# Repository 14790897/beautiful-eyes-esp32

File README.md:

# Beautiful Eyes - 嵌入式眼睛动画项目

一个运行在 ESP32-C3 上的眼睛动画项目，支持多种风格的眼睛效果。双屏同步显示，营造立体生动的眼睛效果。

## ✨ 特性

### 七种眼睛风格

#### 1. 普通眼睛 (Normal Eye)
- 白色眼白，棕色虹膜
- 自然的眨眼动画
- 简单的睫毛和血管纹理
- 标准的眼球移动

#### 2. 恶魔眼睛 (Demon Eye)
- 深灰色巩膜，红色虹膜
- **竖瞳设计** - 猫科动物般的竖直瞳孔
- **发光效果** - 脉动的发光光晕
- **心形高光** - 独特的反光效果
- 更快速、更主动的眼神移动

#### 3. 美丽女生眼睛 (Beautiful Eye)
- 纯净的眼白
- **多层虹膜渐变** - 温柔的棕色渐变
- **淡粉色眼影** - 精致的眼妆效果
- **深棕色眼线** - 从眼头到眼尾的渐变眼线
- **浓密睫毛** - 18根上睫毛 + 12根下睫毛
- **三重高光** - 主高光、淡蓝色次高光、下方小高光
- **闪亮动画** - 虹膜上的动态闪光点
- 温柔优雅的眨眼动画

#### 4. 赛博朋克眼睛 (Cyber Eye) 🆕
- 深蓝灰色巩膜，青色虹膜
- **HUD显示** - 科幻感十足的抬头显示界面
- **扫描线** - 动态扫描线效果
- **网格纹理** - 机械感的虹膜网格
- **数据流动画** - 随机数据流显示
- **准星瞄准** - 红色瞄准准星
- 快速精确的机械眼球移动

#### 5. 星空宇宙眼睛 (Cosmic Eye) 🆕
- 深紫灰巩膜，神秘宇宙色
- **星云渐变** - 多层星云色彩渐变
- **星系旋转** - 虹膜内的星系螺旋效果
- **闪烁星星** - 随机分布的闪烁星点
- **流星划过** - 偶尔出现的流星效果
- **脉冲发光** - 神秘的发光脉动
- 缓慢优雅的眼球移动

#### 6. 显轮眼 (Sharingan - Wheel Eye) 🆕
- 纯白巩膜，鲜红色虹膜
- **三勾玉设计** - 经典的三勾玉图案
- **勾玉旋转** - 持续旋转的勾玉动画
- **红色发光** - 强烈的红色光晕效果
- **黑色轮廓** - 清晰的图案轮廓线
- 凌厉快速的眼神移动

#### 7. 星瞳眼 (Anime Star Pupil Eye) 🆕
- 纯白巩膜，粉紫色虹膜
- **五角星瞳孔** - 可爱的星形瞳孔设计
- **多层渐变** - 粉色系多层虹膜渐变
- **闪烁效果** - 虹膜周围的闪烁星光
- **粉色发光** - 梦幻的粉色光晕
- **星星旋转** - 瞳孔星星的缓慢旋转
- 活泼灵动的眼球移动

### 真实动画效果
- 自然的眨眼动画
- 灵动的眼球移动
- 精致的虹膜渐变
- 多重高光效果
- 双屏同步显示
- **共享 Sprite** - 单个图像缓冲区双屏复用，节省内存

### 简单交互
- **单击** BOOT 按钮 (GPIO9) - 向下翻页(下一个眼睛类型)
- **双击** BOOT 按钮 (GPIO9) - 向上翻页(上一个眼睛类型)
- 即按即切，无需重启
- 可配置的按钮响应参数

## 🔧 硬件要求

- **开发板**: ESP32-C3 (推荐: AirM2M Core ESP32-C3)
- **显示屏**: 2块 ST7789 240x240 LCD (双屏同步显示)
- **数据线**: USB Type-C

### 引脚连接

#### 共享 SPI 引脚
| SPI 引脚 | ESP32-C3 GPIO |
|---------|---------------|
| SCLK    | 2             |
| MOSI    | 3             |

#### 屏幕一引脚
| LCD 引脚 | ESP32-C3 GPIO |
|---------|---------------|
| DC      | 10            |
| CS      | 6             |
| RST     | 7             |

#### 屏幕二引脚
| LCD 引脚 | ESP32-C3 GPIO |
|---------|---------------|
| DC      | 1             |
| CS      | 0             |
| RST     | 4             |

#### 按钮
| 功能     | ESP32-C3 GPIO |
|---------|---------------|
| BOOT 按钮 | 9           |

## 🚀 快速开始

### 方法 1: 下载预编译固件 (推荐)

1. 前往 [Releases](https://github.com/14790897/beautiful-eyes-esp32/releases) 页面
2. 下载最新版本的固件包
3. 解压并按照 `FLASH_GUIDE.md` 说明烧录

**使用 esptool 烧录:**
```bash
pip install esptool

esptool.py --chip esp32c3 --port COM5 --baud 460800 \
  --before default_reset --after hard_reset write_flash \
  0x0 bootloader.bin \
  0x8000 partitions.bin \
  0x10000 firmware.bin
```

### 方法 2: 从源码构建

#### 前置要求
- Python 3.7+
- PlatformIO Core

#### 构建步骤

```bash
# 克隆仓库
git clone https://github.com/14790897/beautiful-eyes-esp32.git
cd beautiful-eyes-esp32

# 安装 PlatformIO
pip install platformio

# 编译
pio run

# 编译并上传
pio run -t upload

# 查看串口输出
pio device monitor
```

## 📖 使用说明

### 切换眼睛类型

#### 单击 BOOT 按钮 (GPIO9) - 向下翻页

```
普通眼睛 → 魅魔眼睛 → 美丽女生眼睛 → 赛博朋克眼睛 → 星空宇宙眼睛 → 显轮眼 → 星瞳眼 → (循环)
```

#### 双击 BOOT 按钮 (GPIO9) - 向上翻页

```
普通眼睛 → 星瞳眼 → 显轮眼 → 星空宇宙眼睛 → 赛博朋克眼睛 → 美丽女生眼睛 → 魅魔眼睛 → (循环)
```

串口会输出当前切换的眼睛类型。

### 双击设置说明

如果双击不灵敏，可以在 `src/main.cpp` 中调整以下参数：

```cpp
bootButton.setClickMs(300);   // 单击判定时间(ms) - 越小越快识别
bootButton.setIdleMs(600);    // 双击间隔时间(ms) - 越大越容易触发
```

## 📁 项目结构

```
beautiful-eyes/
├── .github/
│   └── workflows/          # GitHub Actions CI/CD
│       ├── build.yml       # 自动构建工作流
│       └── release.yml     # 版本发布工作流
├── include/
│   ├── eyes/               # 眼睛模块头文件
│   │   ├── normal/         # 普通眼睛
│   │   ├── demon/          # 魅魔眼睛
│   │   ├── beautiful/      # 美丽女生眼睛
│   │   ├── cyber/          # 赛博朋克眼睛
│   │   ├── cosmic/         # 星空宇宙眼睛
│   │   ├── wheel/          # 显轮眼
│   │   └── star/           # 星瞳眼
│   ├── Config.h            # 全局配置
│   └── Display.h           # 显示驱动
├── src/
│   ├── eyes/               # 眼睛模块实现
│   ├── Display.cpp
│   └── main.cpp
├── docs/
│   ├── FILE_STRUCTURE.md   # 文件结构说明
│   └── CI_CD_GUIDE.md      # CI/CD 指南
└── platformio.ini          # PlatformIO 配置
```

详细说明: [FILE_STRUCTURE.md](docs/FILE_STRUCTURE.md)

## 🔄 CI/CD

本项目使用 GitHub Actions 实现自动化构建和发布:

### 自动构建
- ✅ 推送到 `main` 或 `dev` 分支时自动构建
- ✅ Pull Request 时自动构建验证
- ✅ 构建产物保留 30 天，可在 Actions 页面下载

### 自动发布
- ✅ 创建 Git Tag 自动触发发布流程
- ✅ 自动生成完整的烧录指南
- ✅ 自动打包固件、bootloader、分区表
- ✅ 生成 SHA256 校验和

### 如何发布新版本

```bash
# 创建版本标签
git tag -a v1.0.0 -m "Release version 1.0.0"

# 推送标签触发发布
git push origin v1.0.0
```

详细说明请查看 [CI/CD 指南](docs/CI_CD_GUIDE.md)

## 🛠️ 开发指南

### 添加新的眼睛类型

1. 在 `include/eyes/` 和 `src/eyes/` 创建新目录
2. 创建眼睛数据类 (如 `NewEye.h/cpp`)
3. 创建渲染器 (如 `NewEyeRenderer.h/cpp`)
4. 在 `Config.h` 添加配置参数
5. 在 `main.cpp` 集成新类型

详细步骤: [FILE_STRUCTURE.md](docs/FILE_STRUCTURE.md)

### 自定义配置

编辑 `include/Config.h` 可修改:
- **硬件引脚配置** - 双屏幕的 SPI、DC、CS、RST 引脚
- **颜色配置** - 每种眼睛类型独立的颜色方案
- **动画参数** - 眨眼频率、移动速度、旋转速度等
- **特效参数** - 发光强度、闪烁速度、扫描线速度等
- **睫毛参数** - 数量和长度

编辑 `src/main.cpp` 可修改:
- **按钮响应参数**:
  - `setClickMs()` - 单击判定时间
  - `setIdleMs()` - 双击间隔时间
  - `setDebounceMs()` - 去抖动时间
  - `setPressMs()` - 长按判定时间

### 代码规范

- 使用完整的 include 路径: `#include "eyes/normal/Eye.h"`
- 每种眼睛类型独立目录
- 配置参数统一放在 `Config.h`

## 🐛 故障排除

### 编译错误
```bash
# 清理构建缓存
pio run -t clean
# 重新构建
pio run
```

### 烧录失败
- 确保设备已连接且驱动已安装
- 尝试按住 BOOT 按钮再烧录
- 降低波特率: `pio run -t upload --upload-speed 115200`

### 屏幕无显示
- 检查引脚连接是否正确
- 验证显示屏电源供应
- 查看串口输出: `pio device monitor`

### 眼睛闭合不动
- 这是旧版本的 bug，已在最新版修复
- 更新到最新固件即可

### 双击不工作或难以触发
- 检查串口输出是否有双击日志
- 调整 `setIdleMs()` 参数 (增大到 800 或 1000ms)
- 调整 `setClickMs()` 参数 (减小到 200 或 250ms)
- 确保两次点击间隔在设定时间内
- 示例代码在 `src/main.cpp` 的 `setup()` 函数中

## 📊 性能指标

- **显示屏数量**: 2块 (双屏同步)
- **眼睛类型**: 7种不同风格
- **共享内存**: 单个 sprite 双屏共用，节省内存
- **帧率**: ~20 FPS
- **眨眼间隔**: 2-8秒 (不同眼睛类型可配置)
- **按钮响应**:
  - 单击判定: 300ms
  - 双击间隔: 600ms
  - 去抖动: 50ms

## 🤝 贡献

欢迎贡献! 步骤:

1. Fork 本仓库
2. 创建特性分支 (`git checkout -b feature/AmazingFeature`)
3. 提交更改 (`git commit -m 'Add some AmazingFeature'`)
4. 推送到分支 (`git push origin feature/AmazingFeature`)
5. 开启 Pull Request

## 📝 更新日志

查看 [Releases](https://github.com/14790897/beautiful-eyes-esp32/releases) 获取完整更新日志。

### 最新更新
- ✅ 添加双击向上翻页功能
- ✅ 添加星瞳眼效果 - 五角星瞳孔，粉色梦幻
- ✅ 添加显轮眼效果 - 三勾玉旋转，红色发光
- ✅ 添加星空宇宙眼睛效果 - 星云、星系、流星
- ✅ 添加赛博朋克眼睛效果 - HUD、扫描线、准星
- ✅ 添加美丽女生眼睛效果 - 眼线、眼影、浓密睫毛
- ✅ 双屏同步显示，营造立体效果
- ✅ 重构文件结构，模块化设计
- ✅ 修复眼睛闭合不动的 bug
- ✅ 添加 GitHub Actions CI/CD

## 📄 许可证

本项目采用 MIT 许可证 - 查看 [LICENSE](LICENSE) 了解详情。

## 🙏 致谢

- [LovyanGFX](https://github.com/lovyan03/LovyanGFX) - 强大的图形库
- [OneButton](https://github.com/mathertel/OneButton) - 简单的按钮库
- [PlatformIO](https://platformio.org/) - 优秀的构建系统

## 📧 联系方式

- 提交 Issue: [GitHub Issues](https://github.com/14790897/beautiful-eyes-esp32/issues)

---

⭐ 如果这个项目对你有帮助，请给个 Star!

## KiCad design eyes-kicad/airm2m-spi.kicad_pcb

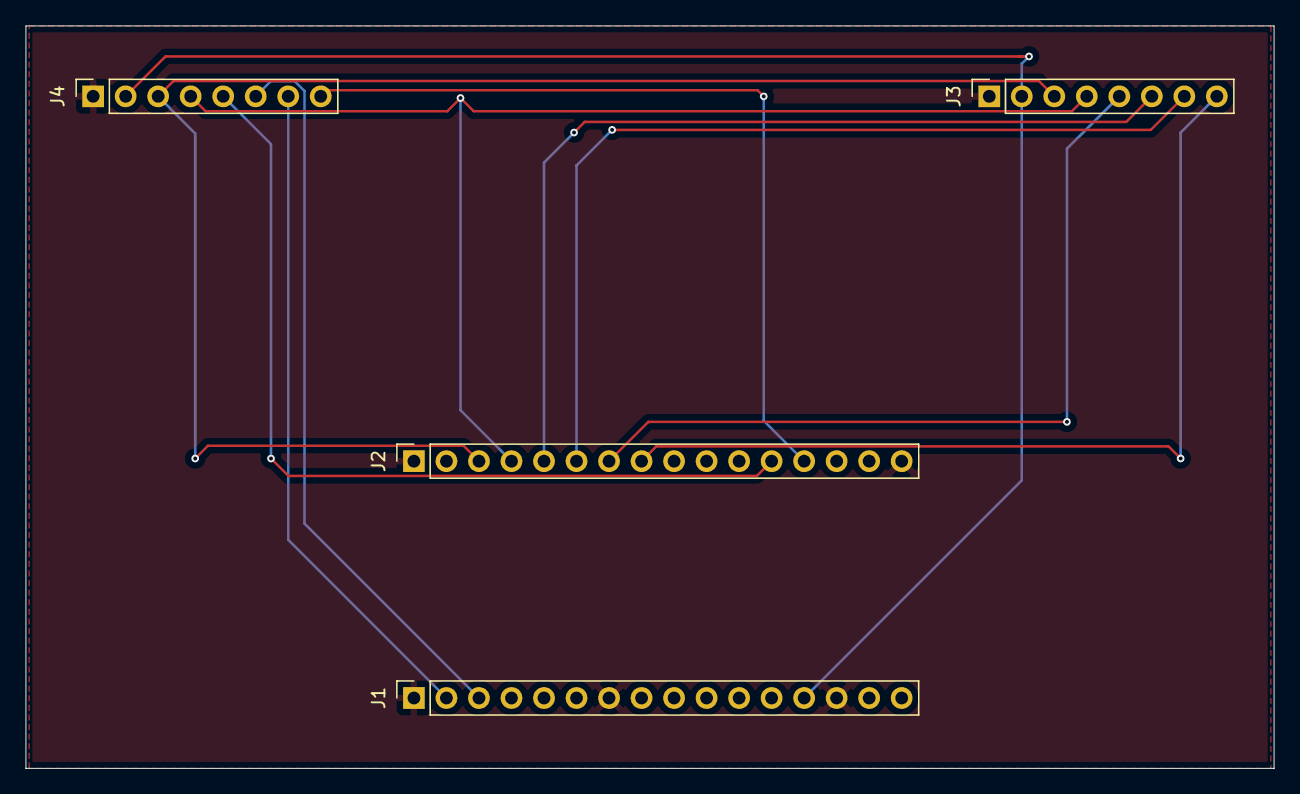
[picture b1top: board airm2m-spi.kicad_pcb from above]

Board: 2 copper layers, 97.5 x 58.0 mm, 4 parts (0 on the bottom side), 12 nets.

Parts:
J1, J2: Conn_01x16; PinSocket_1x16_P2.54mm_Vertical
J3, J4: Conn_01x08; PinSocket_1x08_P2.54mm_Vertical

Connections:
3V3: J1.13, J3.2, J4.2
GND: J1.1, J1.7, J1.14, J2.1, J2.9, J2.16, J3.1, J4.1
unnamed: J2.7, J3.5
unnamed: J2.5, J3.6
unnamed: J2.6, J3.7
unnamed: J2.8, J3.8
unnamed: J2.12, J4.5
unnamed: J1.3, J4.6
unnamed: J1.2, J4.7
unnamed: J2.13, J4.8
SPI_MOSI: J2.4, J3.4, J4.4
SPI_SCLK: J2.3, J3.3, J4.3

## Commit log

2025-10-29 init
2025-10-29 docs
2025-10-30 refractor
2025-10-30 魅魔眼睛初步
2025-10-30 chore
2025-10-30 feat: 共享sprite
2025-10-30 feat: 美丽的眼睛
2025-10-30 refractor: 改变结构
2025-10-30 ci: release
2025-10-30 feat: CyberEyeRenderer
2025-10-30 feat: CosmicEye
2025-11-02 kicad
2025-11-07 chore: kicad
2025-11-07 feat: shared 两个屏幕
2025-11-07 feat: 只创建一个屏幕
2025-11-08 feat: 显轮眼
2025-11-08 feat: 星瞳眼
2025-11-08 feat: 双击功能
2025-11-19 feat: 添加双击向上翻页功能并完善README
2025-11-19 fix: 添加GitHub Actions权限配置
    - 在release.yml和build.yml中添加contents:write权限
    - 修复Resource not accessible by integration错误
    - 更新文档和workflow描述

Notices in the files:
README.md:
License: MIT
